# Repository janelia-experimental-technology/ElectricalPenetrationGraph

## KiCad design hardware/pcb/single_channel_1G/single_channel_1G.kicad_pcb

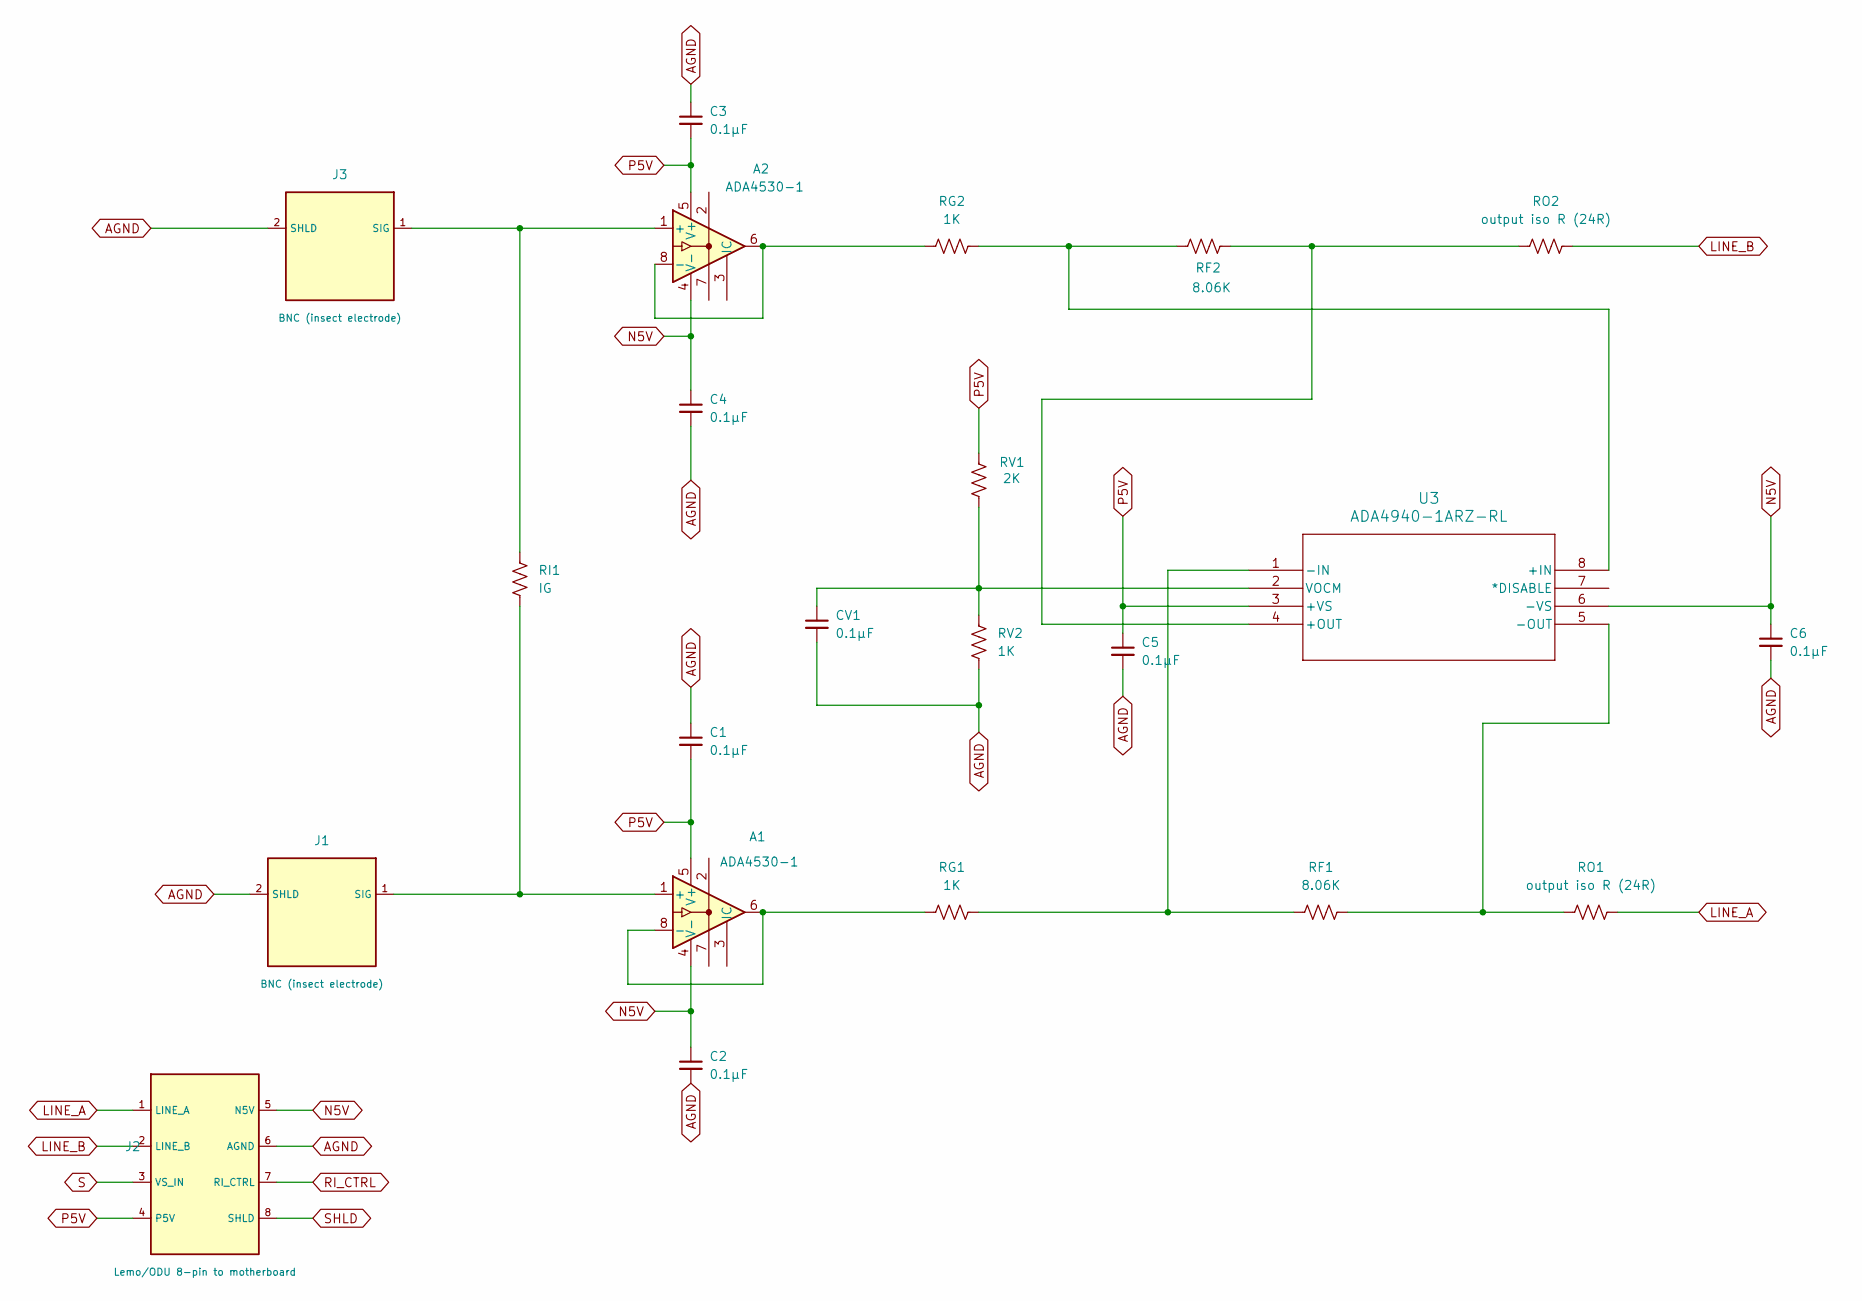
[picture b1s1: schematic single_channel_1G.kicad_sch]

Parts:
A1, A2: ADA4530-1; SOIC-8_3.9x4.9mm_P1.27mm
C1, C2, C3, C4, C5, C6: 0.1µF; C_0603_1608Metric
CV1: 0.1µF; C_0603_1608Metric
J1, J3: BNC (insect electrode); BNC_Amphenol_031-5539_Vertical
J2: Lemo/ODU 8-pin to motherboard; PinHeader_1x08_P2.54mm_Vertical
RF1, RF2: 8.06K; R_0805_2012Metric
RG1, RG2: 1K; R_0805_2012Metric
RI1: IG; R_Axial_DIN0309_L9.0mm_D3.2mm_P20.32mm_Horizontal
RO1, RO2: output iso R (24R); R_0603_1608Metric
RV1: 2K; R_0805_2012Metric
RV2: 1K; R_0805_2012Metric
U3: ADA4940-1ARZ-RL; SOIC-8_5.3x6.2mm_P1.27mm

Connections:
AGND: C1.1, C2.2, C3.1, C4.2, C5.2, C6.2, CV1.2, J1.2 (SHLD), J2.6 (AGND), J3.2 (SHLD), RV2.2
LINE_A: J2.1 (LINE_A), RO1.1
LINE_B: J2.2 (LINE_B), RO2.1
N5V: A1.4 (V-), A2.4 (V-), C2.1, C4.1, C6.1, J2.5 (N5V), U3.6 (-VS)
unnamed: A1.1 (+), J1.1 (SIG), RI1.2
unnamed: A1.6, A1.8 (-), RG1.2
unnamed: A2.1 (+), J3.1 (SIG), RI1.1
unnamed: A2.6, A2.8 (-), RG2.2
unnamed: RF2.2, RG2.1, U3.8 (+IN)
unnamed: RF2.1, RO2.2, U3.4 (+OUT)
unnamed: RF1.2, RG1.1, U3.1 (-IN)
unnamed: RF1.1, RO1.2, U3.5 (-OUT)
unnamed: CV1.1, RV1.2, RV2.1, U3.2 (VOCM)
P5V: A1.5 (V+), A2.5 (V+), C1.2, C3.2, C5.1, J2.4 (P5V), RV1.1, U3.3 (+VS)
RI_CTRL: J2.7 (RI_CTRL)
S: J2.3 (VS_IN)
SHLD: J2.8 (SHLD)

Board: 2 copper layers, 22 parts (0 on the bottom side), 14 nets, no tracks yet.
